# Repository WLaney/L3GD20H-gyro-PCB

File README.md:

# L3GD20H breakout PCB
This is a breakout board for the I2C functionality of the L3GD20H IC gyroscope.
This chip does have SPI and interrupt capabilities, but these are not broken out on this board.

The desgine for this board is dervided from [Adafruits breakout board](https://github.com/adafruit/Adafruit-L3GD20-Breakout-PCB),
the differences are that this board only has I2C capabilities and does not have a voltage regulator. This means that the board should be
powered with 3.3V.

Additionaly this board was desgined in such a way to be pin compatable with [Sparkfun's MMA8452Q breakout board](https://www.sparkfun.com/products/12756). 
These boards can be stacked to help save space in embedded projects.

This board was desgined as part of the Sharkduino Project at The College of William and Mary, more information can be found at [sharkduino.com](http://www.sharkduino.com)

Design/Changes by William Laney,
Original Design by Adafruit Industries.

Creative Commons Attribution, Share-Alike license, check license.txt for more information. All text above must be included in any redistribution.

To order this board from OSH Park please click here:

<a href="https://oshpark.com/shared_projects/uGds3Je4"></img></a>

## Desgine Notes
This is the first PCB I designed and there are some parts of it that I would change, however I have built this board and it functions properly.

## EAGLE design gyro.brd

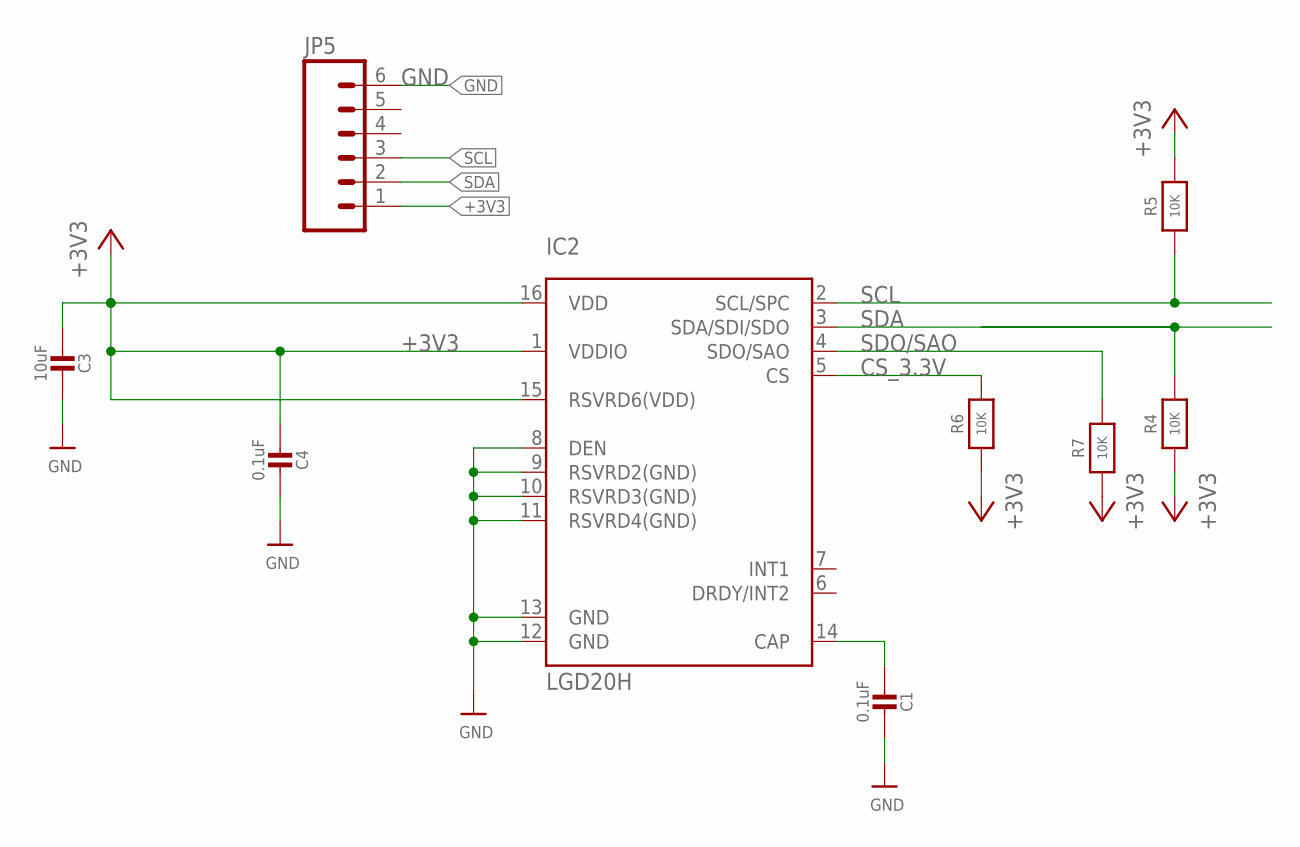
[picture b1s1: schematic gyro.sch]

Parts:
C1, C4: 0.1uF; 0805-NO
C3: 10uF; 0805-NO
IC2: LGD20H; L3GD20H_LGA16L
JP5: M06SIP; 1X06
R4, R5, R7: 10K; 0805-NO
R6: 10K; _0805MP

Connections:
+3V3: C3.2, C4.2, IC2.1 (VDDIO), IC2.15 (RSVRD6(VDD)), IC2.16 (VDD), JP5.1, R4.1, R5.2, R6.1, R7.1
CS_3.3V: IC2.5 (CS), R6.2
GND: C1.1, C3.1, C4.1, IC2.8 (DEN), IC2.9 (RSVRD2(GND)), IC2.10 (RSVRD3(GND)), IC2.11 (RSVRD4(GND)), IC2.12 (GND), IC2.13 (GND), JP5.6
unnamed: C1.2, IC2.14 (CAP)
SCL: IC2.2 (SCL/SPC), JP5.3, R5.1
SDA: IC2.3 (SDA/SDI/SDO), JP5.2, R4.2
SDO/SAO: IC2.4 (SDO/SAO), R7.2

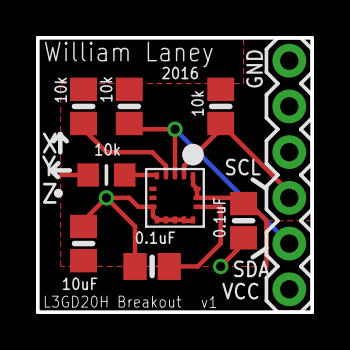
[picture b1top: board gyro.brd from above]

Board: 2 copper layers, 15.2 x 15.2 mm, 9 parts (0 on the bottom side), 7 nets.

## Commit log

2016-06-15 created layout for just the gyro
2016-06-15 boards rounted with silk screen
2016-06-15 shortedn connections, removed via
2016-06-15 rottated header 180 degrees
2016-06-15 added six pin header to stack with accell
2016-06-15 set up pins to line up with accel corectly
2016-06-15 minor placment adjustments
2016-06-16 final touches
2016-06-16 final verson to submit to osh park for protyping
2016-06-16 adjusted tname and tvalue layers
2016-06-17 adjusted silk screen layout
2016-06-30 added bom
2016-07-08 added documintation
2016-07-08 who knows, probably just opened the file
2016-07-11 removed residual layer1 directory
2016-07-11 documentation
2016-07-12 updated documentation with contact info
2016-07-15 Proofread gyroscope/documentation.txt
    Grammar, spelling updates. Clarified nature of axis/rotation labels.
2016-11-29 added package sizes to BOM
    IC size was formely NA now it has the package type of the IC
2017-01-26 added gitignore file
2017-01-26 added ShareAlike licenses
    This desgine is adapted from adafruit so I am using there licenses
2017-01-26 Created Readme
2017-01-26 fixed url
2017-01-26 typo
2017-02-14 added osh order to readme
2017-04-11 minor readme update
    github markdown changeded a little
